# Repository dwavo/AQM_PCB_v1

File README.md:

# AQM_PCB_v1

Thu Oct 15 19:47:02 PDT 2020

printed circuit board from kevin - sent to china for production.  We did version zero on an 'other mill'.  It proved to be a little too fickle. 

This is the first commercially spun pcb board for AQM luft.data project, now known as sensor community: https://sensor.community/ 

CA design PCB-v1 supports NodeMCUv2 and NodeMCUv3 esp8266 microcontroller.  

Set up with DHT and SDS011 sensors, also supports BM*280; and PMSx003 series sniffers.  P1 allows soldering screw terminals or pigtail, with positive shown as +++.  

Top diode (D1) is for reverse polarity protection.  Fusex at .25 Amp.  dc:buck (LM2596) allows external power source of  9-24V dc source (old wall warts) for long runs (over 5 meters).  This solves the potential low voltage problem of driving the 5v fan on the SDS011.  

Using two 1A 40V Shottky diodes (D2,D3) to protect computer if usb and external power are applied at the same time. Test points added for ground, 5v and 3.3v.  

When building these, adjust the lM2596 to 5v at the test point.  Put black fingernail polish or hot glue and label the power converter "5V".    

A second version is contemplated, which will allow mounting the SDS011 on the same board.   
 
comments: dclark@clarkco.com

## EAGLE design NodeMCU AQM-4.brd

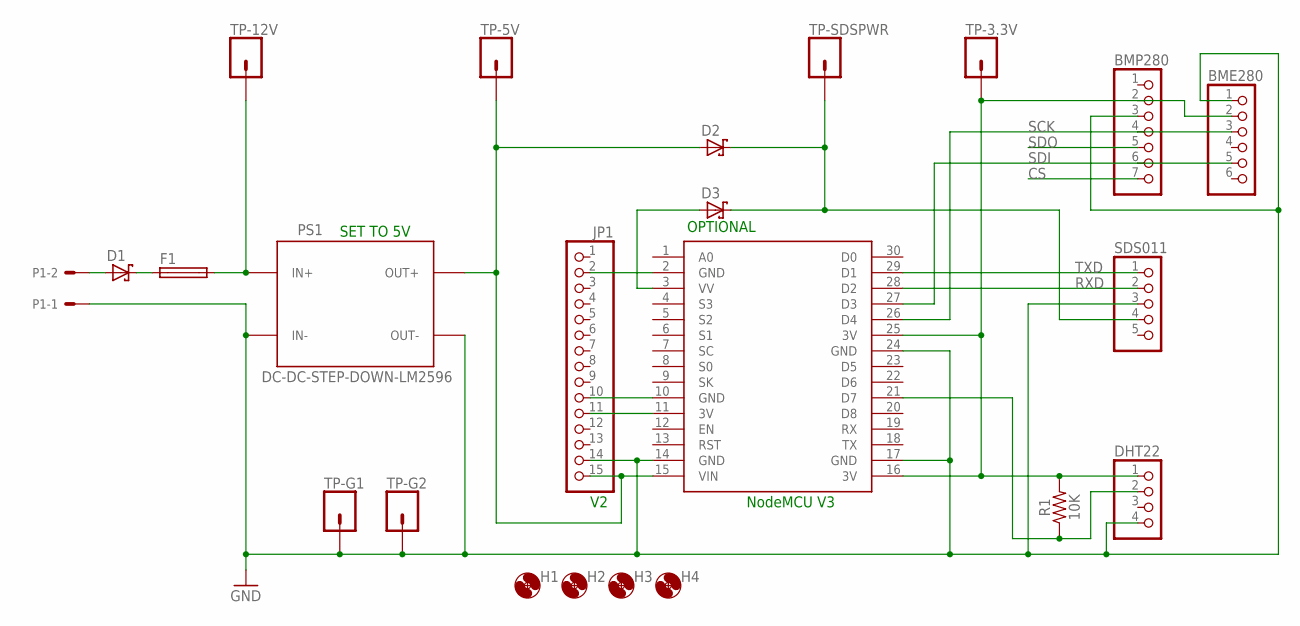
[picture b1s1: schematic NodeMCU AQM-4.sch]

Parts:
BME280: PINHD-1X6; 1X06
BMP280: PINHD-1X7; 1X07
D1, D2, D3: SCHOTTKY-DIODEF126Z12; DIODE_F126Z12
DHT22: PINHD-1X4; 1X04
F1: SH22,5A
H1, H2, H3, H4: MOUNT-HOLE3.6; 3,6
JP1: PINHD-1X15; 1X15
P1: KK-156-2
PS1: DC-DC-STEP-DOWN-LM2596
R1: 10K; AXIAL-0.3
SDS011: PINHD-1X5; 1X05
TP-3.3V, TP-5V, TP-12V: CONN_01OFFSET; 1X01_OFFSET
TP-G1, TP-G2: CONN_01OFFSET; 1X01_OFFSET
TP-SDSPWR: CONN_01OFFSET; 1X01_OFFSET
U$1: NODEMCU

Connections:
3V3: BME280.2, BMP280.2, DHT22.1, JP1.11, R1.P$2 (2), TP-3.3V.1, U$1.11 (3V), U$1.16 (3V), U$1.25 (3V)
CS: BMP280.7
GND: BME280.1, BMP280.3, DHT22.4, JP1.2, JP1.10, JP1.14, P1.1, PS1.IN-, PS1.OUT-, SDS011.3, TP-G1.1, TP-G2.1, U$1.2 (GND), U$1.10 (GND), U$1.14 (GND), U$1.17 (GND), U$1.24 (GND)
unnamed: D2.A (C), JP1.15, PS1.OUT+, TP-5V.1, U$1.15 (VIN)
unnamed: D3.A (C), U$1.3 (VV)
unnamed: D1.A (C), P1.2
unnamed: D1.C (A), F1.1
unnamed: F1.2, PS1.IN+, TP-12V.1
unnamed: DHT22.2, R1.P$1 (1), U$1.21 (D7)
RXD: SDS011.2, U$1.28 (D2)
SCK: BME280.3, BMP280.4, U$1.26 (D4)
SDI: BME280.5, BMP280.6, U$1.27 (D3)
SDO: BMP280.5
SDSPWR: D2.C (A), D3.C (A), SDS011.4, TP-SDSPWR.1
TXD: SDS011.1, U$1.29 (D1)

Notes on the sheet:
SET TO 5V
NodeMCU V3
OPTIONAL

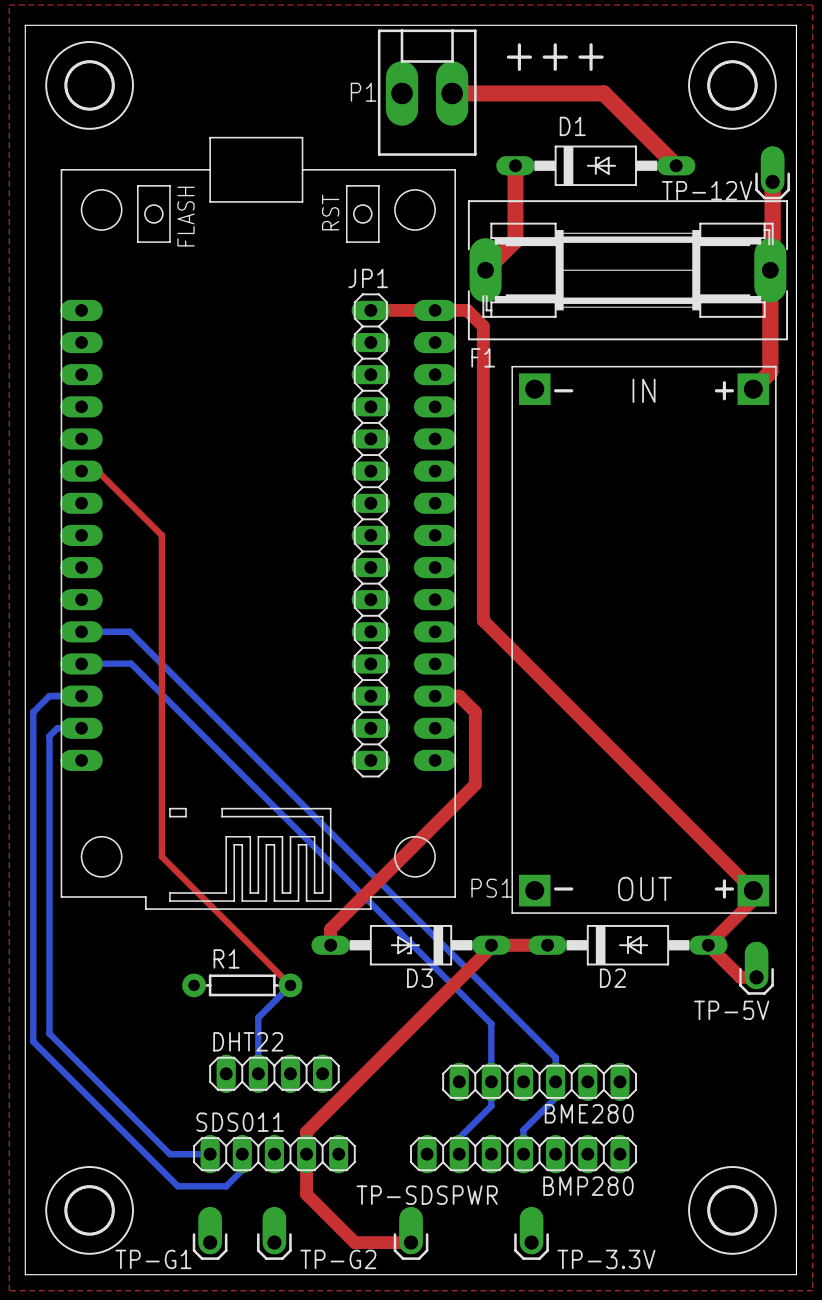
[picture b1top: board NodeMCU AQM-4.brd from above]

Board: 2 copper layers, 60.9 x 98.7 mm, 23 parts (0 on the bottom side), 13 nets.

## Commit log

2020-10-16 PCB_v1
    Initial build sent to china
2020-10-16 pcb board schematics to send out for mfg
    printed circuit board for esp8266 nodeMCU sensor.community luftdata.info

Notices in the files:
parts and their libraries:
diy-modules: Released under the Creative Commons Attribution 4.0 International License: http://creativecommons.org/licenses/by/4.0
SparkFun-Resistors: Licensing: Creative Commons ShareAlike 4.0 International - https://creativecommons.org/licenses/by-sa/4.0
